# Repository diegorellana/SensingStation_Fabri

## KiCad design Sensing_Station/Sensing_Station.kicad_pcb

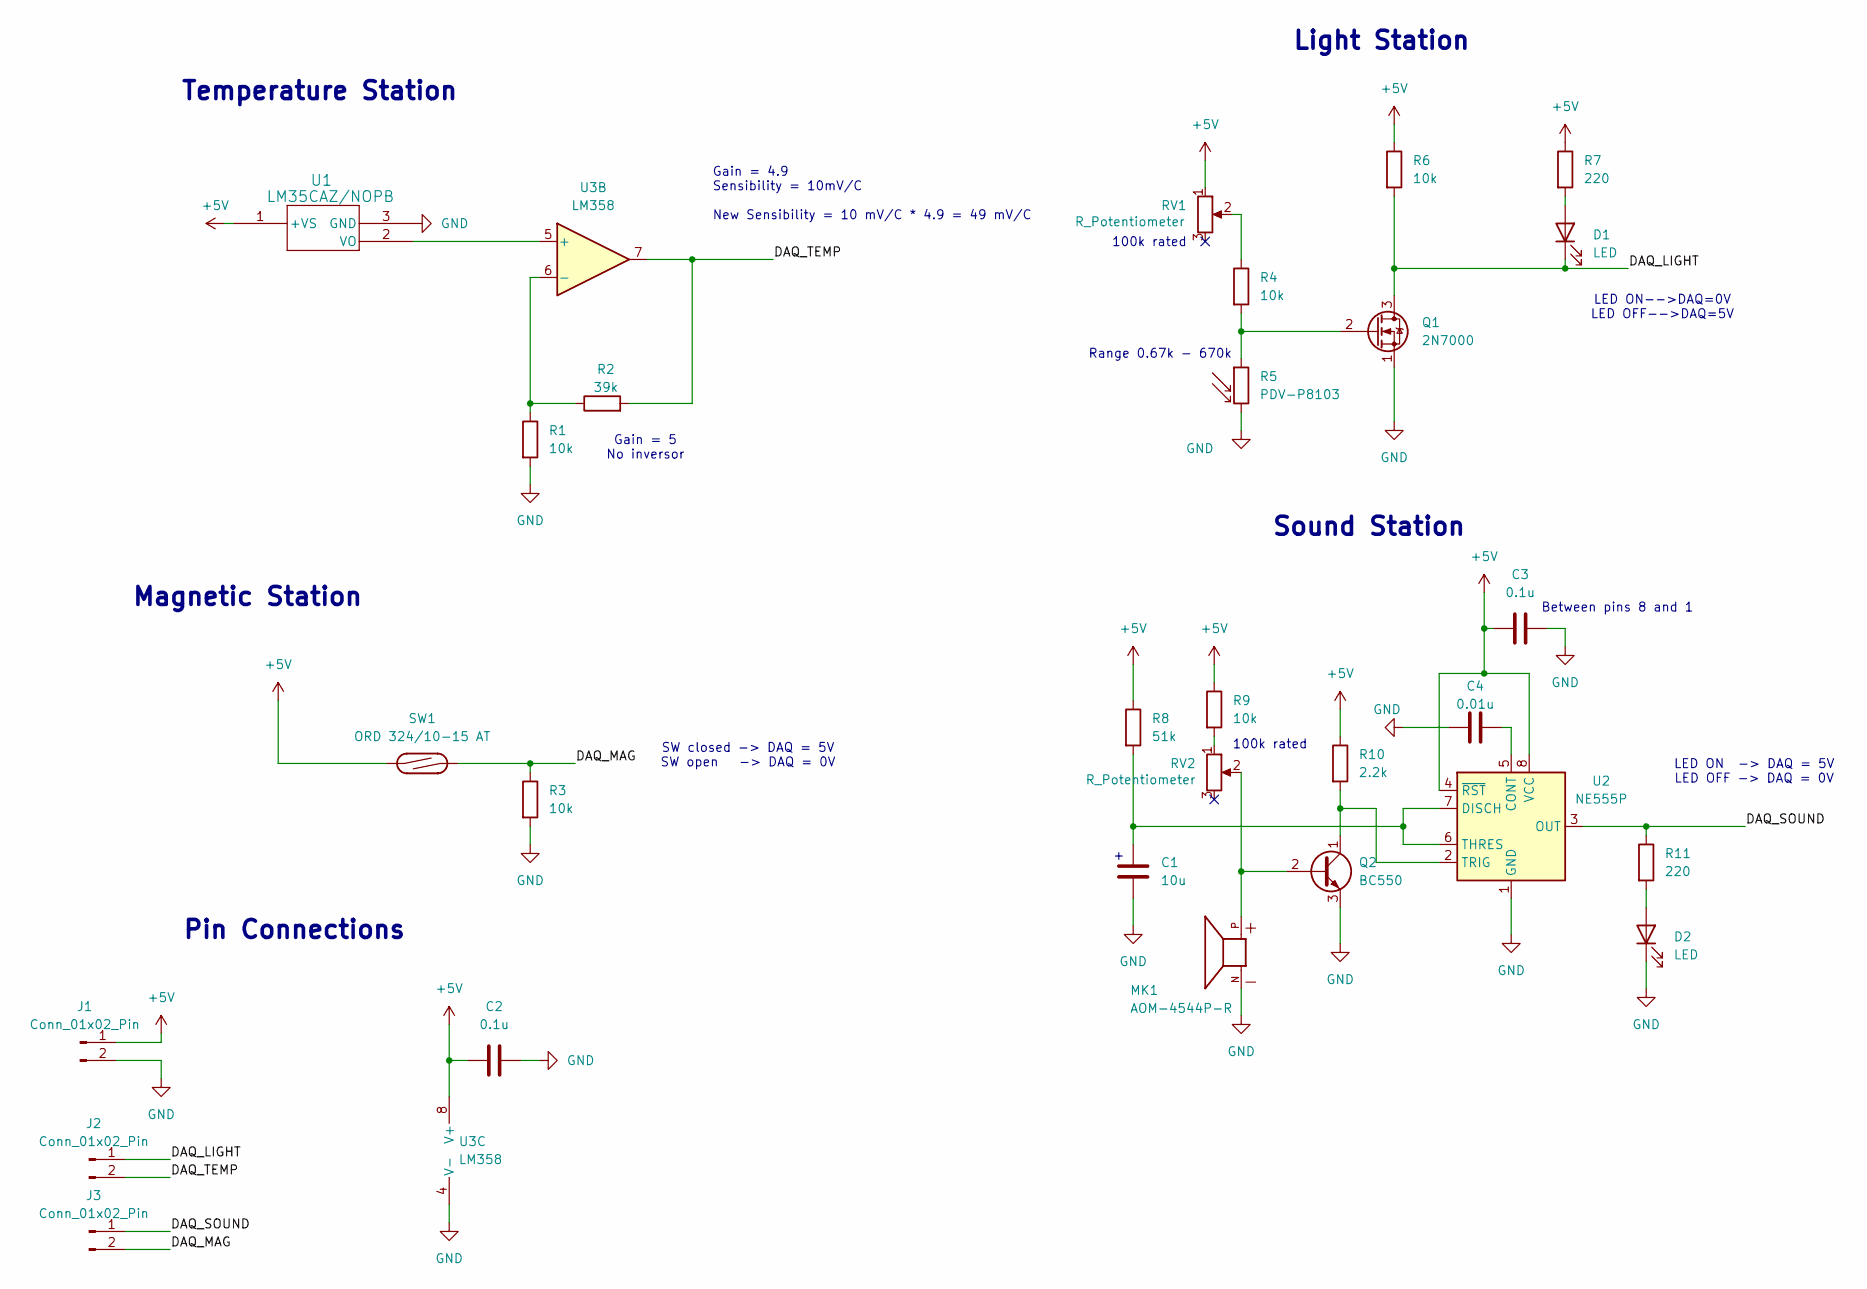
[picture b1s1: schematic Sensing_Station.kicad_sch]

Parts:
C1: 10u; CP_Radial_D5.0mm_P2.00mm
C2, C3: 0.1u; C_Disc_D3.8mm_W2.6mm_P2.50mm
C4: 0.01u; C_Disc_D3.8mm_W2.6mm_P2.50mm
D1, D2: LED; LED_D5.0mm
J1, J2, J3: Conn_01x02_Pin; TerminalBlock_TE_282834-2_1x02_P2.54mm_Horizontal
MK1: AOM-4544P-R; MIC_AOM-4544P-R; PARTREV A
Q1: 2N7000; TO-92_Inline_Wide
Q2: BC550; TO-92_Inline
R1, R3, R4, R6, R9: 10k; R_Axial_DIN0207_L6.3mm_D2.5mm_P10.16mm_Horizontal
R2: 39k; R_Axial_DIN0207_L6.3mm_D2.5mm_P10.16mm_Horizontal
R5: PDV-P8103; PHODET_PDV-P8103
R7, R11: 220; R_Axial_DIN0207_L6.3mm_D2.5mm_P10.16mm_Horizontal
R8: 51k; R_Axial_DIN0207_L6.3mm_D2.5mm_P10.16mm_Horizontal
R10: 2.2k; R_Axial_DIN0207_L6.3mm_D2.5mm_P10.16mm_Horizontal
RV1, RV2: R_Potentiometer; Potentiometer_Bourns_3296W_Vertical
SW1: ORD 324/10-15 AT; ORD324_P20.32mm
U1: LM35CAZ/NOPB; TO-92_Inline
U2: NE555P; DIP-8_W7.62mm
U3: LM358; DIP-8_W7.62mm

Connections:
+5V: C2.1, C3.1, J1.1, R6.1, R7.1, R8.1, R9.1, R10.1, RV1.1, SW1.1, U1.1 (+VS), U2.4 (~RST), U2.8 (VCC), U3.8 (V+)
/DAQ_LIGHT: D1.1 (K), J2.1, Q1.3 (D), R6.2
/DAQ_MAG: J3.2, R3.1, SW1.2
/DAQ_SOUND: J3.1, R11.1, U2.3 (OUT)
/DAQ_TEMP: J2.2, R2.2, U3.7
GND: C1.2, C2.2, C3.2, C4.1, D2.1 (K), J1.2, MK1.N, Q1.1 (S), Q2.3 (E), R1.2, R3.2, R5.2, U1.3 (GND), U2.1 (GND), U3.4 (V-)
unnamed: D1.2 (A), R7.2
unnamed: D2.2 (A), R11.2
unnamed: Q1.2 (G), R4.2, R5.1
unnamed: MK1.P, Q2.2 (B), RV2.2
unnamed: Q2.1 (C), R10.2, U2.2 (TRIG)
unnamed: R4.1, RV1.2
unnamed: R9.2, RV2.1
unnamed: U1.2 (VO), U3.5 (+)
unnamed: C4.2, U2.5 (CONT)
unnamed: C1.1, R8.2, U2.6 (THRES), U2.7 (DISCH)
unnamed: R1.1, R2.1, U3.6 (-)

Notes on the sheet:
Magnetic Station
Light Station
Range 0.67k - 670k
Between pins 8 and 1
Gain = 4.9 Sensibility = 10mV/C New Sensibility = 10 mV/C * 4.9 = 49 mV/C
100k rated
Sound Station
Gain = 5 No inversor
SW closed -> DAQ = 5V SW open -> DAQ = 0V
Temperature Station
LED ON-->DAQ=0V LED OFF-->DAQ=5V
LED ON -> DAQ = 5V LED OFF -> DAQ = 0V
Pin Connections

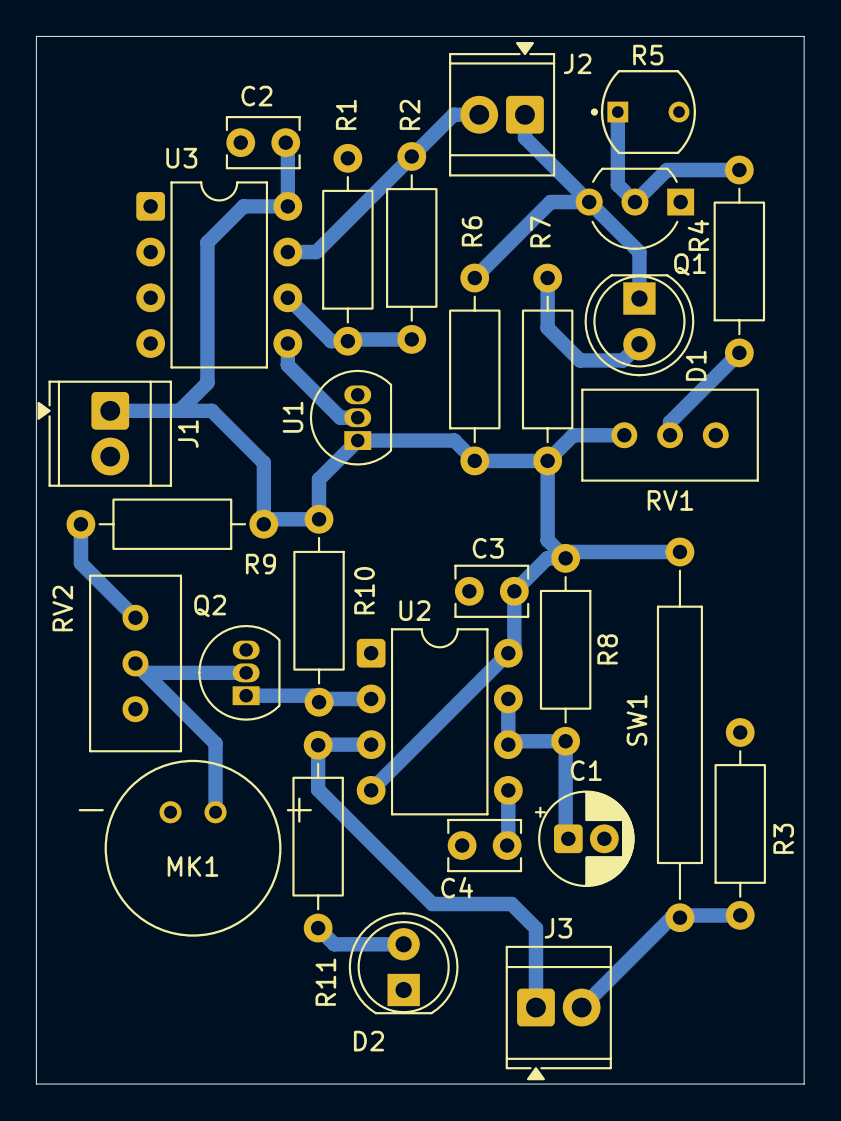
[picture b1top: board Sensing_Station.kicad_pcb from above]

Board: 2 copper layers, 42.7 x 58.2 mm, 29 parts (0 on the bottom side), 17 nets.
